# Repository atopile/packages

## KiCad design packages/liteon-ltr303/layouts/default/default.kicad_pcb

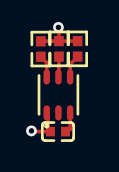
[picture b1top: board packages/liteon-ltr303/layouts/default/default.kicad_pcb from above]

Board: 2 copper layers, 5 parts (0 on the bottom side), 5 nets.

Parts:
C1: [capacitance: unknown]; C0402
R1, R2, R3: [resistance: unknown]; R0402
U1: TDFN-6_L2.0-W2.0-P0.65-BL

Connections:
INT: R1.1, U1.5
SCL: R2.1, U1.4
SDA: R3.1, U1.6
hv: C1.1, R1.2, R2.2, R3.2, U1.1
lv: C1.2, U1.3

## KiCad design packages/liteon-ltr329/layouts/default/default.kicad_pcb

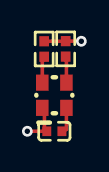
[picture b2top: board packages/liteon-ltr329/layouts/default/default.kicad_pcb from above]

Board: 2 copper layers, 4 parts (0 on the bottom side), 4 nets.

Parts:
C1: [capacitance: unknown]; C0402
R1, R2: [resistance: unknown]; R0402
U1: LED-SMD_4P-L2.0-W2.0-P1.20-S1.35

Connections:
SCL: R1.1, U1.4
SDA: R2.1, U1.3
hv: C1.1, R1.2, R2.2, U1.1
lv: C1.2, U1.2
